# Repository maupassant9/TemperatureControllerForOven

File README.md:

# TemperatureControllerForOven
Temperature Controller for oven with ESP8266

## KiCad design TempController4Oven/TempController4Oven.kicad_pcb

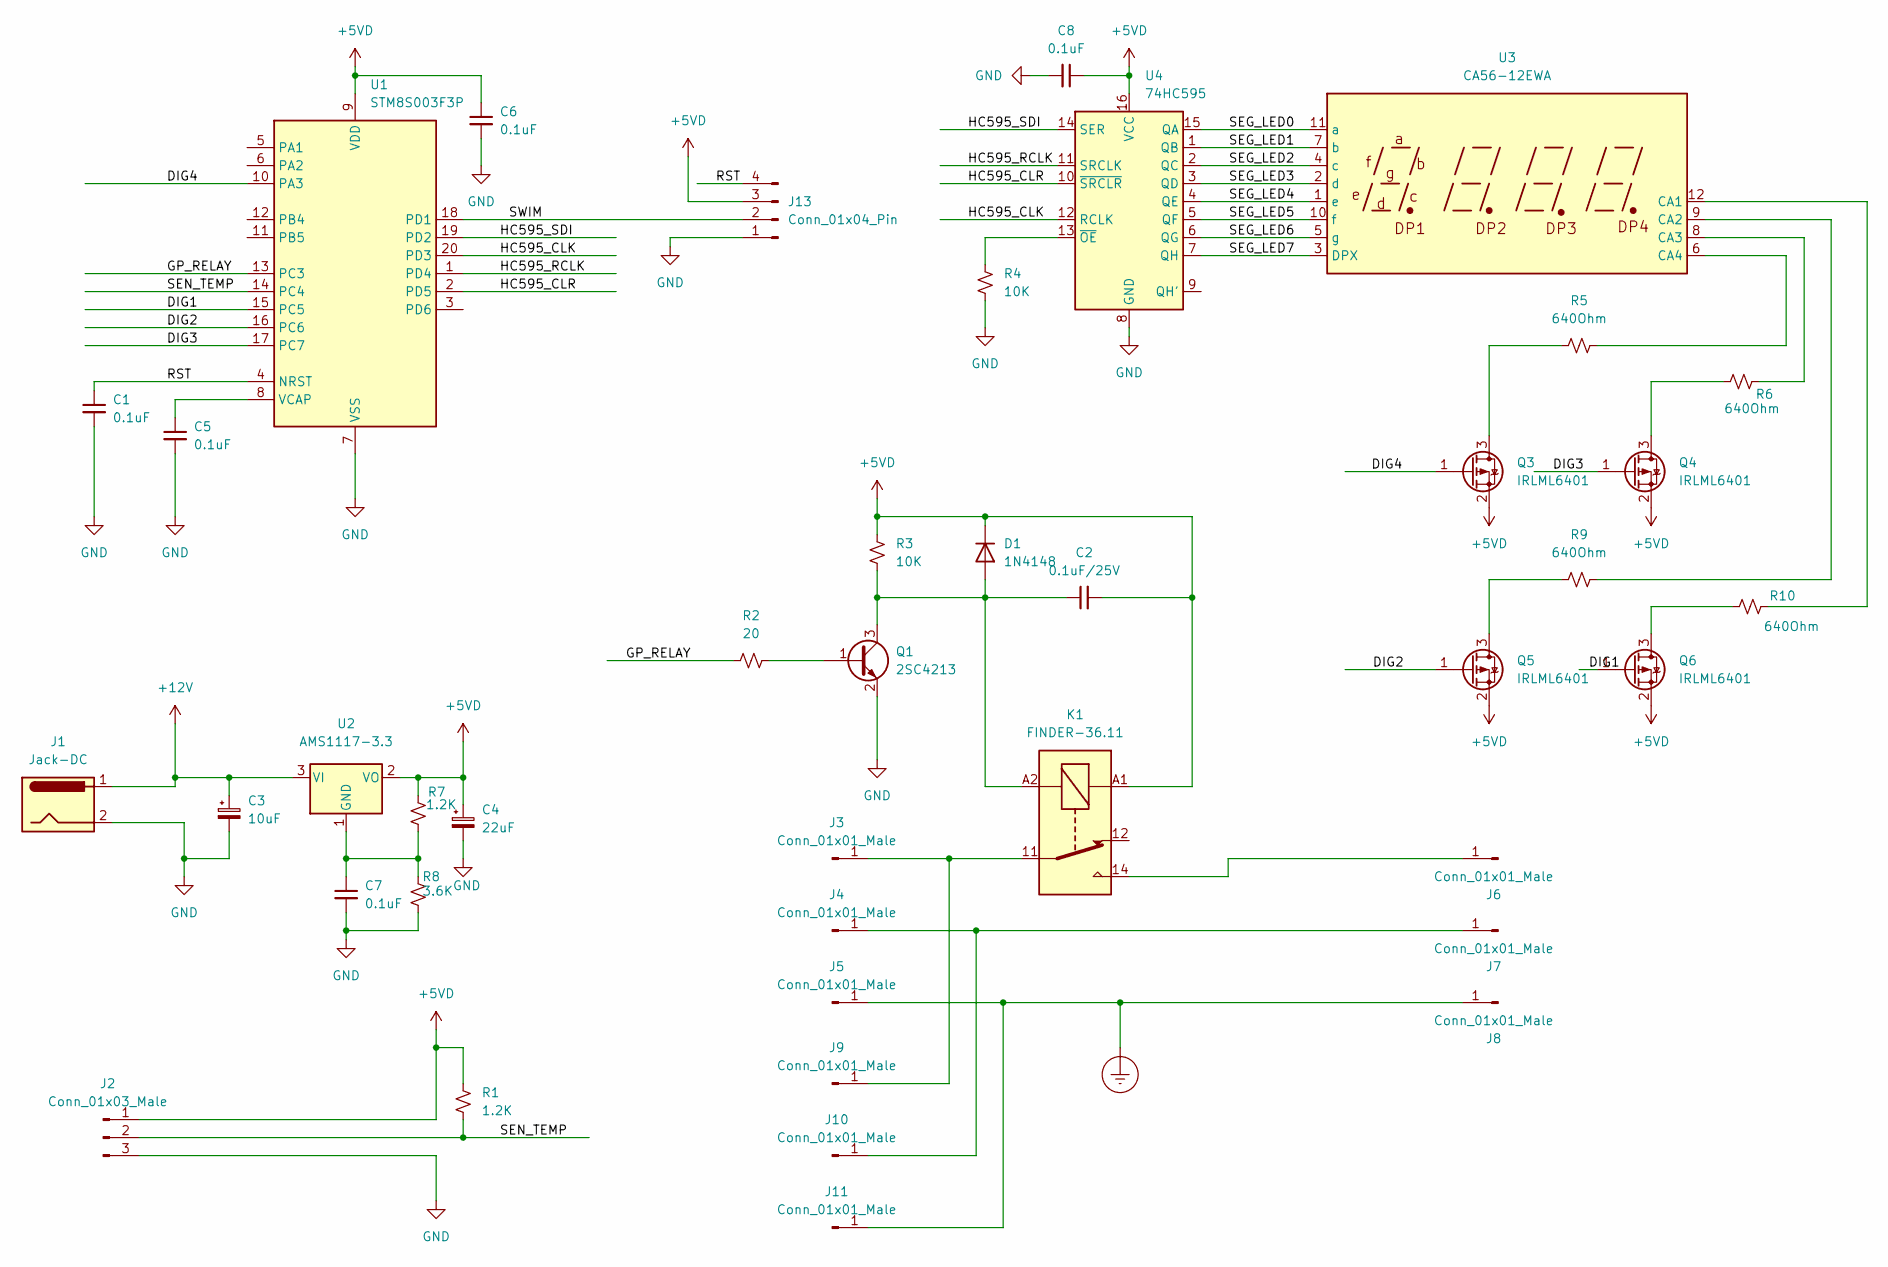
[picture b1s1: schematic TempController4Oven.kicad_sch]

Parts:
C1, C5, C6, C7, C8: 0.1uF; C_0805_2012Metric_Pad1.18x1.45mm_HandSolder
C2: 0.1uF/25V; C_0805_2012Metric_Pad1.18x1.45mm_HandSolder
C3: 10uF; CP_Radial_D5.0mm_P2.50mm
C4: 22uF; CP_Radial_D5.0mm_P2.50mm
D1: 1N4148; D_DO-35_SOD27_P7.62mm_Horizontal
J1: Jack-DC; PinHeader_1x02_P2.54mm_Vertical
J2: Conn_01x03_Male; PinHeader_1x03_P2.54mm_Vertical
J3, J4, J5, J6, J7, J8, J9, J10, J11: Conn_01x01_Male; Pin_D1.3mm_L11.0mm
J13: Conn_01x04_Pin; PinHeader_1x04_P2.54mm_Vertical
K1: FINDER-36.11; Relay_SPDT_Finder_36.11
Q1: 2SC4213; SOT-323_SC-70
Q3, Q4, Q5, Q6: IRLML6401; SOT-23
R1, R7: 1.2K; R_0805_2012Metric_Pad1.20x1.40mm_HandSolder
R2: 20; R_0805_2012Metric_Pad1.20x1.40mm_HandSolder
R3, R4: 10K; R_0805_2012Metric_Pad1.20x1.40mm_HandSolder
R5, R6, R9, R10: 640Ohm; R_0805_2012Metric_Pad1.20x1.40mm_HandSolder
R8: 3.6K; R_0805_2012Metric_Pad1.20x1.40mm_HandSolder
U1: STM8S003F3P; TSSOP-20_4.4x6.5mm_P0.65mm
U2: AMS1117-3.3; SOT-223-3_TabPin2
U3: CA56-12EWA; HSN3642BS
U4: 74HC595; SOIC-16_3.9x9.9mm_P1.27mm

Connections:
+5VD: C2.2, C4.1, C6.1, C8.1, D1.1 (K), J2.1, J13.3, K1.A1, Q3.2 (S), Q4.2 (S), Q5.2 (S), Q6.2 (S), R1.2, R3.1, R7.2, U1.9 (VDD), U2.2 (VO), U4.16 (VCC)
+12V: C3.1, J1.1, U2.3 (VI)
/DIG1: Q6.1 (G), U1.15 (PC5)
/DIG2: Q5.1 (G), U1.16 (PC6)
/DIG3: Q4.1 (G), U1.17 (PC7)
/DIG4: Q3.1 (G), U1.10 (PA3)
/GP_RELAY: R2.1, U1.13 (PC3)
/HC595_CLK: U1.20 (PD3), U4.12 (RCLK)
/HC595_CLR: U1.2 (PD5), U4.10 (~SRCLR)
/HC595_RCLK: U1.1 (PD4), U4.11 (SRCLK)
/HC595_SDI: U1.19 (PD2), U4.14 (SER)
/RST: C1.1, J13.4, U1.4 (NRST)
/SEG_LED0: U3.11 (a), U4.15 (QA)
/SEG_LED1: U3.7 (b), U4.1 (QB)
/SEG_LED2: U3.4 (c), U4.2 (QC)
/SEG_LED3: U3.2 (d), U4.3 (QD)
/SEG_LED4: U3.1 (e), U4.4 (QE)
/SEG_LED5: U3.10 (f), U4.5 (QF)
/SEG_LED6: U3.5 (g), U4.6 (QG)
/SEG_LED7: U3.3 (DPX), U4.7 (QH)
/SEN_TEMP: J2.2, R1.1, U1.14 (PC4)
/SWIM: J13.2, U1.18 (PD1)
Earth_Protective: J5.1 (Pin_1_1), J8.1 (Pin_1_1), J11.1 (Pin_1_1)
GND: C1.2, C3.2, C4.2, C5.2, C6.2, C7.2, C8.2, J1.2, J2.3, J13.1, Q1.2 (E), R4.2, R8.1, U1.7 (VSS), U4.8 (GND)
unnamed: C2.1, D1.2 (A), K1.A2, Q1.3 (C), R3.2
unnamed: J3.1 (Pin_1_1), J9.1 (Pin_1_1), K1.11
unnamed: J6.1 (Pin_1_1), K1.14
unnamed: J4.1 (Pin_1_1), J7.1 (Pin_1_1), J10.1 (Pin_1_1)
unnamed: Q1.1 (B), R2.2
unnamed: Q3.3 (D), R5.1
unnamed: Q4.3 (D), R6.1
unnamed: Q5.3 (D), R9.1
unnamed: Q6.3 (D), R10.1
unnamed: C5.1, U1.8 (VCAP)
unnamed: C7.1, R7.1, R8.2, U2.1 (GND)
unnamed: R10.2, U3.12 (CA1)
unnamed: R9.2, U3.9 (CA2)
unnamed: R6.2, U3.8 (CA3)
unnamed: R5.2, U3.6 (CA4)
unnamed: R4.1, U4.13 (~OE)

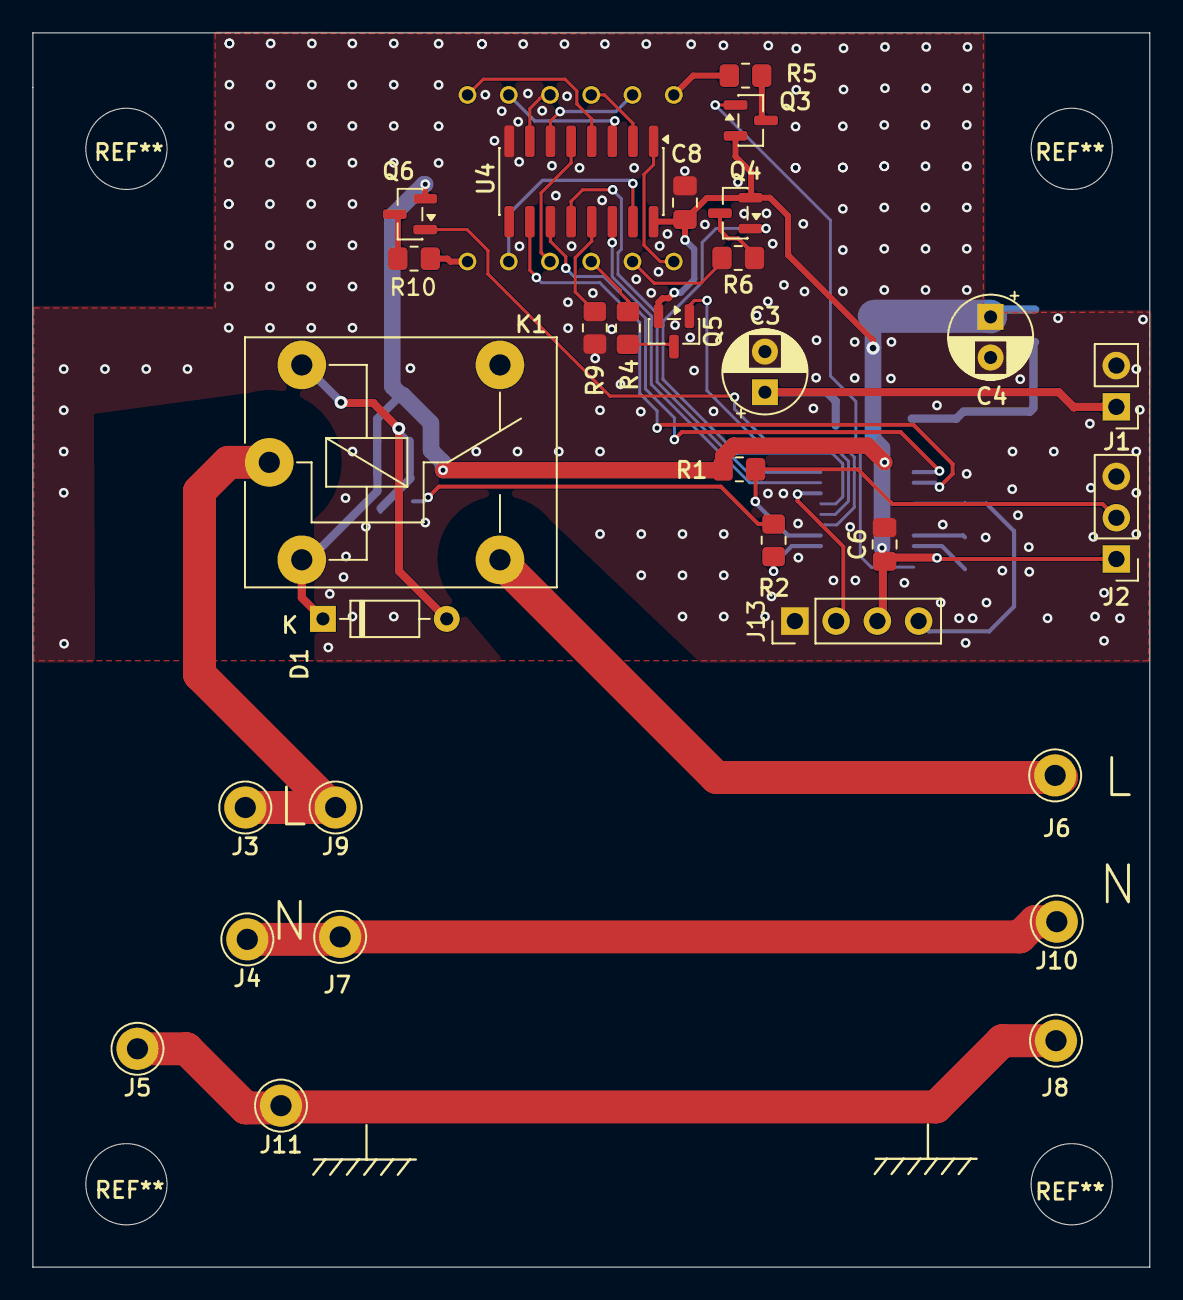
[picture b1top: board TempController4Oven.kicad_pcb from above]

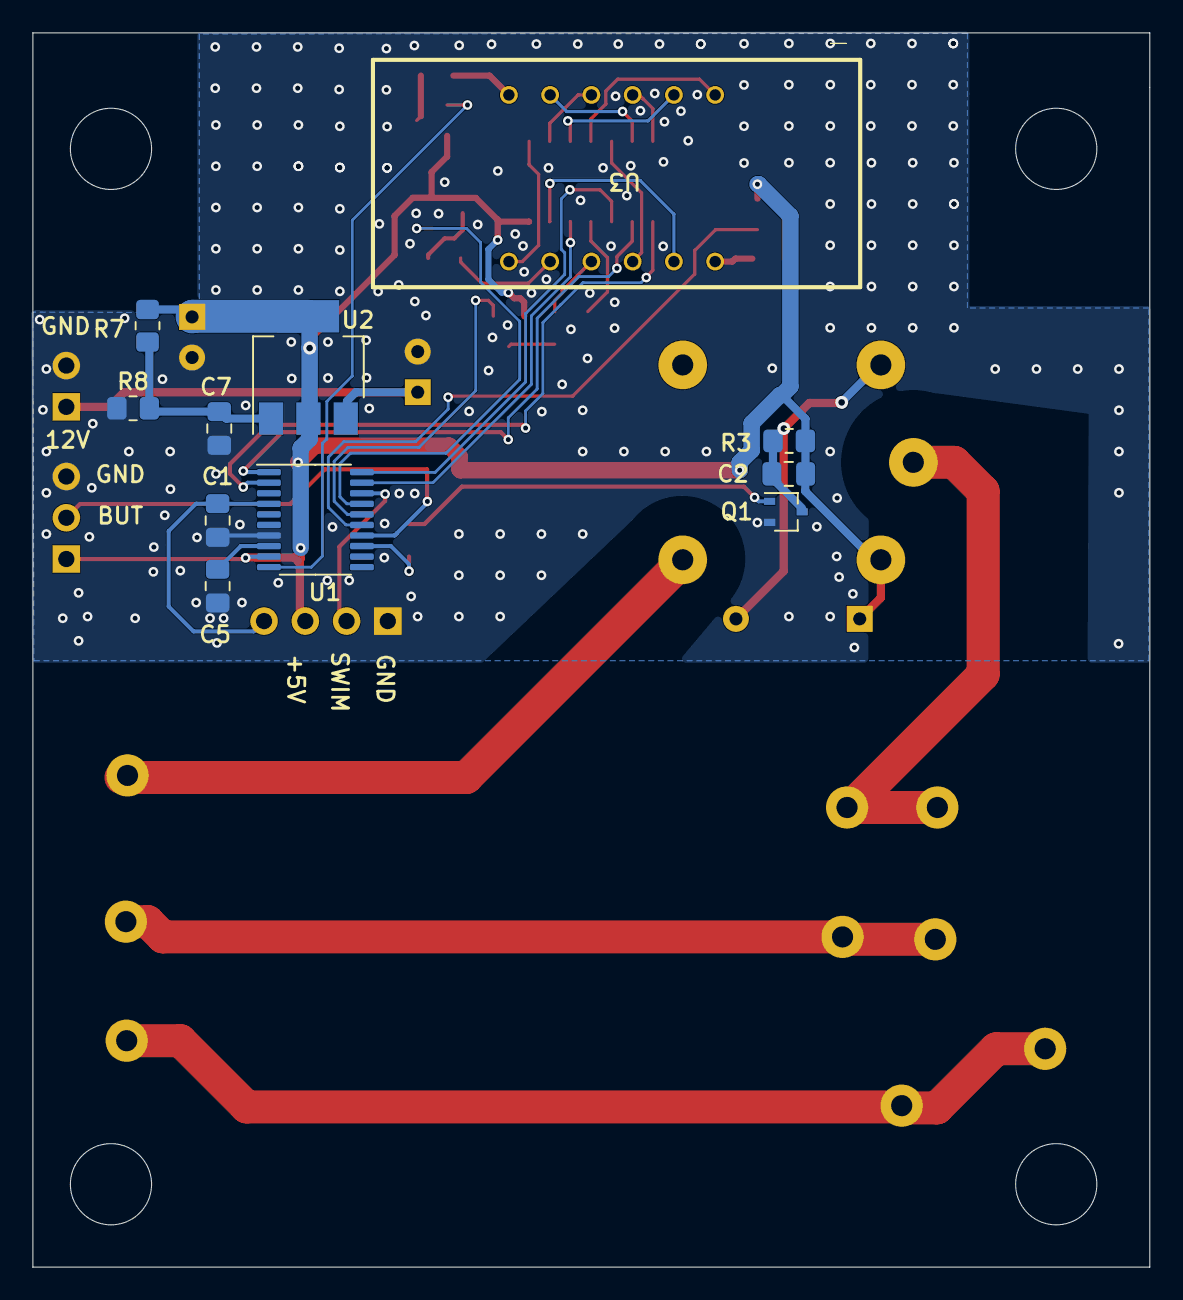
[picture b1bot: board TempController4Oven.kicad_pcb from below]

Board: 2 copper layers, 68.8 x 76.0 mm, 41 parts (11 on the bottom side), 40 nets.

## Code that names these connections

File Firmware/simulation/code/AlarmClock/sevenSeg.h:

/*
* FileName: 7seg.h
* Author: Dong Xia
* This is source file of the driver of 7seg.h 
* using 74HC595.
* The connection between 74HC595 and 7seg:
* A(P10) - QB
* B(P9) - QC
* C(P7) - QD
* D(P5) - QE
* E(P4) - QF
* F(P2) - QG
* G(P1) - QH
* DP(P6) - QA
*
* Change Records:
*      >> (30/Dec/2017): Creation of file
*
*/

#ifndef _7SEG_H
#define _7SEG_H
/********************************************
* Include
********************************************/
#include "74hc595.h"

/********************************************
* Macro
********************************************/
#define DISP_DIGITAL_NO 4

#define DIG1_PIN (3)
#define DIG2_PIN (4)
#define DIG3_PIN (5)
#define DIG4_PIN (6)
/********************************************
* External Variables
********************************************/


/********************************************
* Type definition
********************************************/


/********************************************
* Function prototype
********************************************/
/*------------------------------------------------
 * Drv7SegInit();
 * Initialize the 7Seg Device.
 * This function just call the init function 
 * of 74HC595.
 * Paras:
 *  >> hc595_handle_t*: a handle pointer to 74Hc595
 * Return:
 *  >> 
 * Change Records:
 *  >> (30/Dec/2017): Create the function
 *----------------------------------------------*/
 void Drv7SegInit(hc595_handle_t *handle);

/*------------------------------------------------
 * Drv7SegDisp();
 * Display the number 
 * Paras:
 *  >> hc595_handle_t*: a handle pointer to 74Hc595
 *  >> unsigned char: the number to display, should be
 *     between 0-9.
 * Return:
 *  >> 
 * Change Records:
 *  >> (30/Dec/2017): Create the function
 *----------------------------------------------*/
void Drv7SegSetDigit(hc595_handle_t *handle, 
								uint8_t digit,
								uint8_t devId);

void Drv7SegSetRawCode(hc595_handle_t *handle, 
	uint8_t code,
	uint8_t devId);
								
void Drv7SegSetNum(hc595_handle_t * handle, int16_t num);
/*------------------------------------------------
 * Drv7SegDispWithDp();
 * Display the number 
 * Paras:
 *  >> hc595_handle_t*: a handle pointer to 74Hc595
 *  >> unsigned char: the number to display, should be
 *     between 0-9, and this function will also display
 *     the point.
 * Return:
 *  >> 
 * Change Records:
 *  >> (30/Dec/2017): Create the function
 *----------------------------------------------*/
void Drv7SegSetDp(hc595_handle_t *handle,
									uint8_t devId);
									
void Drv7SegShow(hc595_handle_t * handle,
									uint8_t devId);
									
void Drv7SegClear(hc595_handle_t *handle, uint8_t devId);
void Drv7SegClearAll(hc595_handle_t *handle);
uint8_t Drv7SegGetDisplayCode(uint8_t devId);
void Drv7SegCtrSet(uint8_t pinNum, bool is_on);
//void DrvLedControl(hc595_handle_t *handle, uint8_t ledNo, bool isOn);
//void DrvDispTemp(hc595_handle_t * handle, int8_t temp);
//bool DrvDispTemp(hc595_handle_t * handle, int16_t temp, uint8_t unit);
//void DrvDispTemp_unsafe(hc595_handle_t * handle, int16_t temp, uint8_t unit);


//void DrvGetLedState(hc595_handle_t *handle, uint8_t ledNo);
#endif

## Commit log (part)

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2023-07-05 Add project
2023-07-06 Add esp-01 into pcb
2023-07-09 Add software matlab app designer, matlab script, python script
2023-07-09 Add new software
2023-07-09 Add new pcb
2023-07-10 Add compatiability for matlab < 2020b
2023-11-02 Add softwares
